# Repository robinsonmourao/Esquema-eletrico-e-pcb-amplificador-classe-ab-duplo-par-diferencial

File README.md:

# 3.0
## SCHEME

## PCB
### ORIGINAL

### INVERTIDO HORIZONTALMENTE

## MODELO FÍSICO
### SUPERIOR
`Desatualizado`

### INFERIOR
`Desatualizado`

# 2.1 beta - 2.0
## SCHEME

## PCB
### ORIGINAL

### INVERTIDO HORIZONTALMENTE

## MODELO FÍSICO
### SUPERIOR 2.1 beta
`versão não funcionou`

### INFERIOR 2.1 beta
`versão não funcionou`

### SUPERIOR 2.0

### INFERIOR 2.0

# 1.0
## SCHEME

## PCB
### ORIGINAL

### INVERTIDO HORIZONTALMENTE

## MODELO FÍSICO
### SUPERIOR
`INEXISTENTE`
### INFERIOR
`25-0-25`_1

`25-0-25`_2

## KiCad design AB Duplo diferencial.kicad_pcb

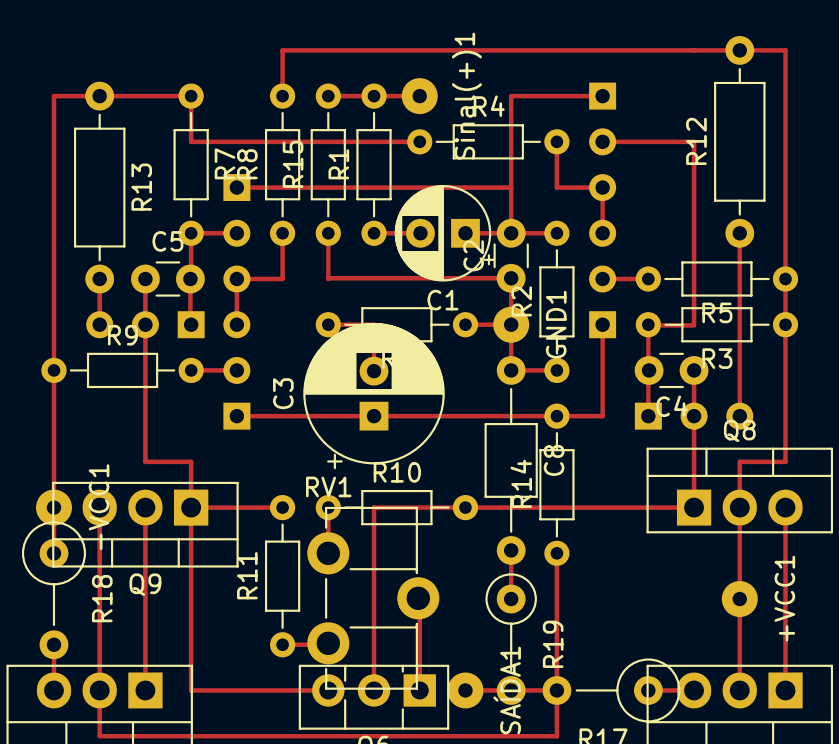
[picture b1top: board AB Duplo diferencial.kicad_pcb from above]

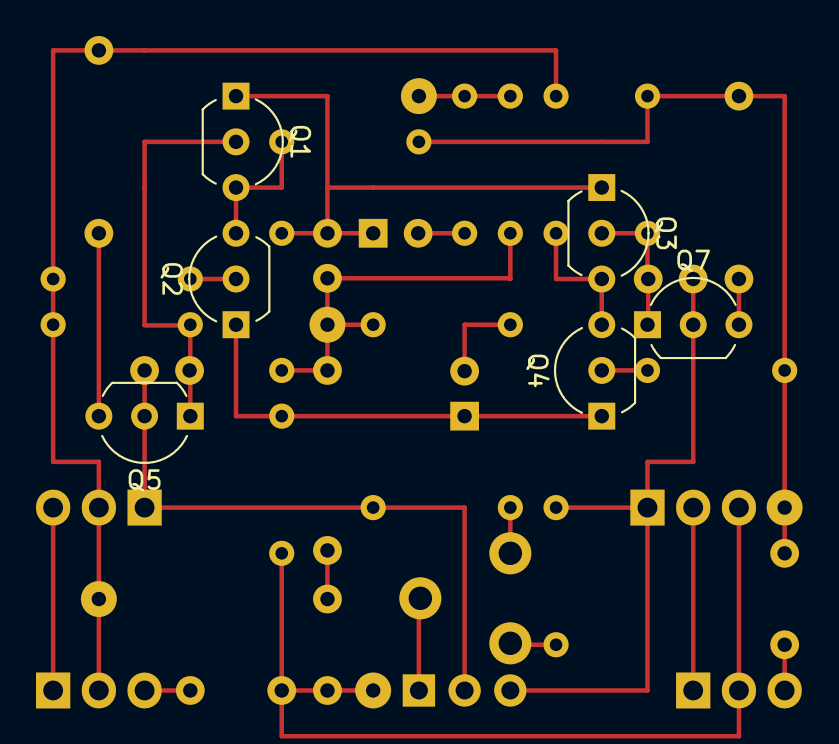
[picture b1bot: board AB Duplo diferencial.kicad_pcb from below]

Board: 2 copper layers, 41 parts (6 on the bottom side), 27 nets.

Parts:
+VCC1: +24; SolderWirePad_1x01_Drill0.8mm
-VCC1: -24; SolderWirePad_1x01_Drill0.8mm
C1: 2.2uf; CP_Radial_D5.0mm_P2.50mm
C2: 100pf; C_Disc_D3.0mm_W1.6mm_P2.50mm
C3: 47uf; CP_Radial_D7.5mm_P2.50mm
C4, C5: 47pf; C_Disc_D3.0mm_W1.6mm_P2.50mm
C8: 0,1uf; C_Axial_L3.8mm_D2.6mm_P10.00mm_Horizontal
GND1: GND; SolderWirePad_1x01_Drill0.8mm
Q1, Q2, Q7: C945; TO-92_Inline_Wide
Q3, Q4, Q5: A733; TO-92_Inline_Wide
Q6: C945; TO-126-3_Vertical
Q8: TIP41; TO-220-3_Vertical
Q9: TIP42; TO-220-3_Vertical
Q10, Q11: 13007; TO-220-3_Vertical
R1, R6: 2k; R_Axial_DIN0204_L3.6mm_D1.6mm_P7.62mm_Horizontal
R2, R4, R8, R14: 47k; R_Axial_DIN0204_L3.6mm_D1.6mm_P7.62mm_Horizontal
R3, R5, R7, R9: 4,7k; R_Axial_DIN0204_L3.6mm_D1.6mm_P7.62mm_Horizontal
R10: 1k; R_Axial_DIN0204_L3.6mm_D1.6mm_P7.62mm_Horizontal
R11: 680r; R_Axial_DIN0204_L3.6mm_D1.6mm_P7.62mm_Horizontal
R12, R13: 2k; R_Axial_DIN0207_L6.3mm_D2.5mm_P10.16mm_Horizontal
R15: 10k; R_Axial_DIN0204_L3.6mm_D1.6mm_P7.62mm_Horizontal
R17, R18: 0.33r; R_Axial_DIN0309_L9.0mm_D3.2mm_P5.08mm_Vertical
R19: 10r; R_Axial_DIN0207_L6.3mm_D2.5mm_P5.08mm_Vertical
RV1: Trimpot; Potentiometer_ACP_CA9-H5_Horizontal
SAÍDA1: Falante; SolderWirePad_1x01_Drill0.8mm
Sinal(+)1: P2(+); SolderWirePad_1x01_Drill0.8mm

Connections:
Earth: C2.1, C8.1, GND1.1, R2.1, R6.1, R15.1
unnamed: +VCC1.1, Q8.2, Q10.2, R3.1, R5.1, R8.2, R12.2
unnamed: -VCC1.1, R4.1, R7.1, R9.1, R13.1, R18.1
unnamed: C1.1, C2.2, Q1.1, Q3.1, R2.2
unnamed: C1.2, R1.1
unnamed: C3.1, Q2.1, Q4.1, R14.2
unnamed: C3.2, R6.2
unnamed: C4.1, Q5.2, Q6.2, Q8.1, R10.2
unnamed: C4.2, Q1.2, Q5.1, R3.2
unnamed: C5.1, Q6.3, Q7.2, Q9.1, R11.2
unnamed: C5.2, Q3.2, Q7.1, R7.2
unnamed: C8.2, R19.1
unnamed: Q1.3, Q2.3, R4.2
unnamed: Q2.2, R5.2
unnamed: Q3.3, Q4.3, R8.1
unnamed: Q4.2, R9.2
unnamed: Q5.3, R12.1
unnamed: Q6.1, RV1.2
unnamed: Q7.3, R13.2
unnamed: Q8.3, Q10.1
unnamed: Q10.3, R17.1
unnamed: Q9.2, Q11.1
unnamed: Q9.3, Q11.2, R14.1, R17.2, R19.2, SAÍDA1.1
unnamed: Q11.3, R18.2
unnamed: R1.2, R15.2, Sinal(+)1.1
unnamed: R10.1, RV1.1
unnamed: R11.1, RV1.3

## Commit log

2024-02-25 Otimizadas algumas trilhas & adicionado resistor 4.7k da entrada pro terra para reduzir o ruído de 60hz
2024-02-25 Alteradas rotas para R7 e R11 & expandido placa geral 1 furo para esquerda
2024-02-25 Reordenação de 20 para 17 linhas na vertical para encaixar dois projetos em uma placa de 15x34
2024-03-16 [trocados de posição] C4 e Q5, C5 e Q7 para que a filtragem do capacitor venha antes da base [otimizado] R5 direto para Q2 [rotacionado] R3 para mesma orientação de R5 [encurtado] trilha entre -VCC e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
2024-03-16 [centralizados] Nomes nos próprios componentes do pcb
2024-03-17 [atualizados] Valores: C7(47uf) & R2/R14(100k) & R12/R13(2K) & R15(10K) [renomeados] "Sinal(+)" para "P2" & +VCC1 para "+24" & "-VCC1" para "-24" & "SAÍDA" para "Falante"
2024-03-30 [rotacionados] C3 e R6 para facilitar a ligação entre Q2 e Q4
2024-04-06 [rollback] R2 & R14 pra 47k [alterado] C4 & C5 pra 47pf
2024-04-06 [atualizado] C4, C5, R2 & R14 no Readme.md
2024-04-06 [desabilitado] camadas F.SilkS, B.CrtYd e B.Fab de PcbView
2024-04-06 [corrigido] TO-92_Inline pra TO-92_Inline_Wide & visão 3d no PcbView
2024-04-06 [corrigido] Readme.md TO-92_Inline pra TO-92_Inline_Wide & visão 3d no PcbView
2024-04-07 [Alterado] versão 3.0 beta para 2.1 beta
2024-08-11 [corrigido][esquema][layout]R12 & R13 de 2k para 1k [removido][esquema][layout]R19 & C8
